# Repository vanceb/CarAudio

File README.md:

# CarAudio
Car Audio Using Raspberry Pi and a DAB Radio board

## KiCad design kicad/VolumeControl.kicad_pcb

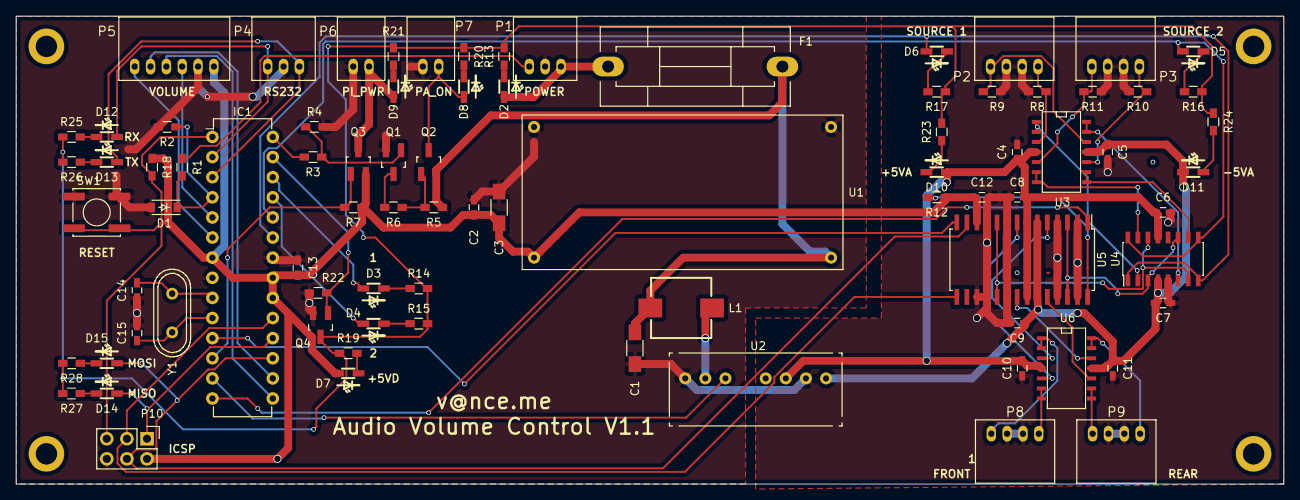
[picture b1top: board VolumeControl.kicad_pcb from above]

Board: 2 copper layers, 160.0 x 59.1 mm, 83 parts (0 on the bottom side), 70 nets.

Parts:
C1: 0.68u; C_1206_HandSoldering
C2, C4, C5, C6, C7, C8, C9, C10, C11, C12, C13: 0.1u; C_0603_HandSoldering
C3: 1u; C_1206_HandSoldering
C14, C15: 22p; C_0603_HandSoldering
D1: 5.1V; SOD-123
D2: +12V; LED_SMD_1.6x0.8mm
D3: 1; LED_SMD_1.6x0.8mm
D4: 2; LED_SMD_1.6x0.8mm
D5: S2; LED_SMD_1.6x0.8mm
D6: S1; LED_SMD_1.6x0.8mm
D7: +5VD; LED_SMD_1.6x0.8mm
D8: PA; LED_SMD_1.6x0.8mm
D9: PI; LED_SMD_1.6x0.8mm
D10: +5VA; LED_SMD_1.6x0.8mm
D11: -5VA; LED_SMD_1.6x0.8mm
D12: RX; LED_SMD_1.6x0.8mm
D13: TX; LED_SMD_1.6x0.8mm
D14: MISO; LED_SMD_1.6x0.8mm
D15: MOSI; LED_SMD_1.6x0.8mm
F1: 1A; Fuseholder5x20_horiz_SemiClosed_Casing10x25mm
IC1: ATMEGA328P-P; DIP-28_W7.62mm
L1: 10u; Inductor_SRR0735A
P1: PWR_IN; JST-3RA
P2: SOURCE_1; JST-4RA
P3: SOURCE_2; JST-4RA
P4: RS232; JST-3RA
P5: VOL_KNOB; JST-6RA
P6: PI_PWR; JST-2RA
P7: PA_EN; JST-2RA
P8: FRONT; JST-4RA
P9: REAR; JST-4RA
P10: ICSP; Pin_Header_Straight_2x03
Q1: BC848B; SOT-23_Handsoldering
Q2, Q3: NX2301P; SOT-23_Handsoldering
Q4: TSM2302CX; SOT-23_Handsoldering
R1, R3, R4, R5, R7, R18, R22: 10k; R_0603_HandSoldering
R2, R6: 22k; R_0603_HandSoldering
R8, R9, R10, R11, R12: 47k; R_0603_HandSoldering
R13, R20: 1k; R_0603_HandSoldering
R14, R15, R16, R17, R19, R21, R23, R24, R25, R26, R27, R28: 220; R_0603_HandSoldering
SW1: SW_PUSH; SW_SPST_EVPBF
U1: Buck_Converter
U2: TMR_3-1221; TMR_3
U3, U6: OPA1664; SOIC-14_N
U4: DG308; SOIC-16_3.9x9.9mm_Pitch1.27mm
U5: PGA4311; SOIC-28_7.5x17.9mm_Pitch1.27mm
Y1: 16MHz; Crystal_HC49-U_Vertical

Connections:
+5VA: C4.1, C6.1, C8.1, C10.1, D10.2, U2.6, U3.4, U4.13, U5.7, U5.22, U6.4
+5VD: C2.1, C3.1, C12.1, C13.1, D7.2, IC1.7, IC1.20, IC1.21, P5.1, P10.2, Q3.2, R7.2, R12.1, R18.1, U1.3, U5.12
-5VA: C5.2, C7.2, C9.2, C11.2, D11.1, U2.8, U3.11, U4.4, U5.6, U5.23, U6.11
/Audio Processing/CS: IC1.11, U5.14
/Audio Processing/LEFT_FRONT: P8.1, U6.1, U6.2
/Audio Processing/LEFT_REAR: P9.1, U6.8, U6.9
/Audio Processing/MUTE: IC1.14, U5.1
/Audio Processing/RIGHT_FRONT: P8.4, U6.6, U6.7
/Audio Processing/RIGHT_REAR: P9.4, U6.13, U6.14
/Audio Processing/SCLK: IC1.19, P10.3, U5.15
/Audio Processing/SDI: D15.2, IC1.17, P10.4, U5.13
/Audio Processing/SOURCE_1_ENABLE: D6.2, IC1.23, U4.1, U4.8
/Audio Processing/SOURCE_1_LEFT: P2.1, R8.1, U3.3
/Audio Processing/SOURCE_1_RIGHT: P2.4, R9.1, U3.12
/Audio Processing/SOURCE_2_ENABLE: D5.2, IC1.24, U4.9, U4.16
/Audio Processing/SOURCE_2_LEFT: P3.1, R10.1, U3.10
/Audio Processing/SOURCE_2_RIGHT: P3.4, R11.1, U3.5
/DIgital_Control/AUDIO_ENABLE: IC1.13, U2.3
/DIgital_Control/BTN: IC1.5, P5.3
/DIgital_Control/IGNITION: D1.1, IC1.4, R1.2, R2.1
/DIgital_Control/MISO: D14.2, IC1.18, P10.1
/DIgital_Control/NEO: IC1.6, P5.6
/DIgital_Control/PA_ENABLE: IC1.28, R3.2
/DIgital_Control/PI_ENABLE: IC1.12, Q3.1, R7.1
/DIgital_Control/RESET: IC1.1, P10.5, R18.2, SW1.2
/DIgital_Control/ROT_A: IC1.15, P5.4
/DIgital_Control/ROT_B: IC1.16, P5.5
/DIgital_Control/RX_IN: D12.2, IC1.2, P4.3
/DIgital_Control/TX_OUT: D13.2, IC1.3, P4.1
/Power/+5V_PI: D9.2, P6.1, Q3.3
/Power/+12V_IGNITION: P1.3, R1.1
/Power/+12V_PA_ENABLE: D8.2, P7.1, Q2.3
/Power/+12V_SUPPLY: D2.2, F1.1, P1.1
GND: C1.2, C2.2, C3.2, C4.2, C5.1, C6.2, C7.1, C8.2, C9.1, C10.2, C11.1, C12.2, C13.2, C14.1, C15.1, D1.2, IC1.8, IC1.22, P1.2, P2.2, P2.3, P3.2, P3.3, P4.2, P5.2, P6.2, P7.2, P8.2, P8.3, P9.2, P9.3, P10.6, Q1.2, Q4.2, R2.2, R4.2, R8.2, R9.2, R10.2, R11.2, R22.2, SW1.1, U1.2, U1.4, U2.1, U2.7, U4.5, U5.2, U5.4, U5.9, U5.11, U5.17, U5.18, U5.20, U5.25, U5.27
LED_GND: Q4.3, R13.2, R14.2, R15.2, R16.2, R17.2, R19.2, R20.1, R21.2, R23.2, R24.2, R25.2, R26.2, R27.2, R28.2
unnamed: C1.1, F1.2, L1.1, Q2.2, R5.1, U1.1
unnamed: C14.2, IC1.9, Y1.1
unnamed: C15.2, IC1.10, Y1.2
unnamed: D2.1, R13.1
unnamed: D3.1, R14.1
unnamed: D3.2, IC1.26
unnamed: D4.1, R15.1
unnamed: D4.2, IC1.25
unnamed: D5.1, R16.1
unnamed: D6.1, R17.1
unnamed: D7.1, R19.1
unnamed: D8.1, R20.2
unnamed: D9.1, R21.1
unnamed: D10.1, R23.1
unnamed: D11.2, R24.1
unnamed: D12.1, R25.1
unnamed: D13.1, R26.1
unnamed: D14.1, R27.1
unnamed: D15.1, R28.1
unnamed: IC1.27, Q4.1, R22.1
unnamed: L1.2, U2.2
unnamed: Q1.1, R3.1, R4.1
unnamed: Q1.3, R6.2
unnamed: Q2.1, R5.2, R6.1
unnamed: R12.2, U5.28
unnamed: U3.1, U3.2, U4.2
unnamed: U3.6, U3.7, U4.15
unnamed: U3.8, U3.9, U4.10
unnamed: U3.13, U3.14, U4.6
unnamed: U4.3, U4.11, U5.3, U5.26
unnamed: U4.7, U4.14, U5.10, U5.19
unnamed: U5.5, U6.3
unnamed: U5.8, U6.5
unnamed: U5.21, U6.12
unnamed: U5.24, U6.10

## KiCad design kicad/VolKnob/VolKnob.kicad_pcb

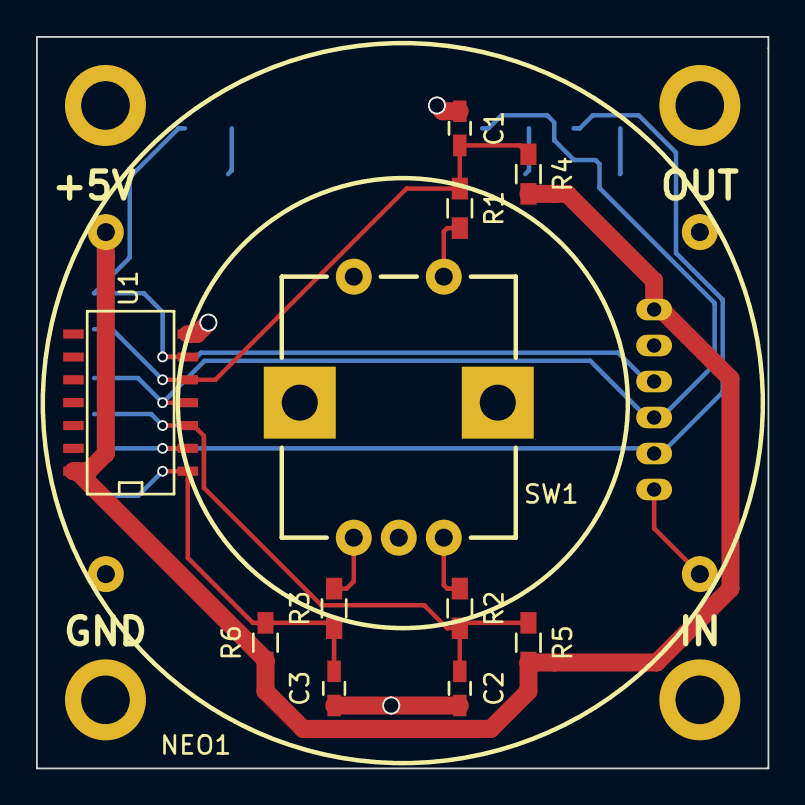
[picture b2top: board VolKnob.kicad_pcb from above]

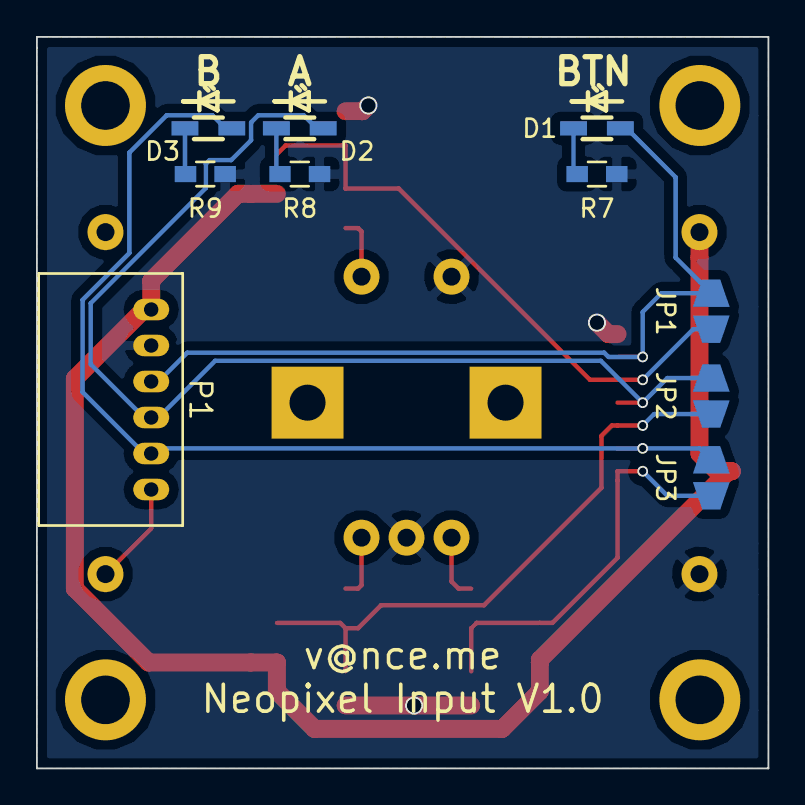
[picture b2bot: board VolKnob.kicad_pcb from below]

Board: 2 copper layers, 40.6 x 40.6 mm, 22 parts (10 on the bottom side), 15 nets.

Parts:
C1, C2, C3: 100n; C_0603_HandSoldering
D1, D2, D3: LED; LED_SMD_1.6x0.8mm
JP1, JP2, JP3: Jumper_NO_Small; Jumper_NO
NEO1: Neopixel; NeoPixel_Ring_12
P1: CONNECTOR; JST-6RA
R1, R2, R3: 2k2; R_0603_HandSoldering
R4, R5, R6: 10k; R_0603_HandSoldering
R7, R8, R9: 220; R_0603_HandSoldering
SW1: Rotary_Encoder
U1: 74HC14; SOIC-14_N

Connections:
+5V: NEO1.1, P1.1, R4.1, R5.1, R6.1, U1.14
/Btn: D1.2, JP1.2, P1.3, U1.6
/NEO: NEO1.3, P1.6
/ROT_A: D2.2, JP2.2, P1.4, U1.4
/ROT_B: D3.2, JP3.2, P1.5, U1.2
GND: C1.2, C2.2, C3.2, NEO1.2, P1.2, R7.1, R8.1, R9.1, SW1.2, SW1.4, U1.7
unnamed: C1.1, JP1.1, R1.1, R4.2, U1.5
unnamed: C2.1, JP2.1, R2.1, R5.2, U1.3
unnamed: C3.1, JP3.1, R3.1, R6.2, U1.1
unnamed: D1.1, R7.2
unnamed: D2.1, R8.2
unnamed: D3.1, R9.2
unnamed: R1.2, SW1.1
unnamed: R2.2, SW1.3
unnamed: R3.2, SW1.5

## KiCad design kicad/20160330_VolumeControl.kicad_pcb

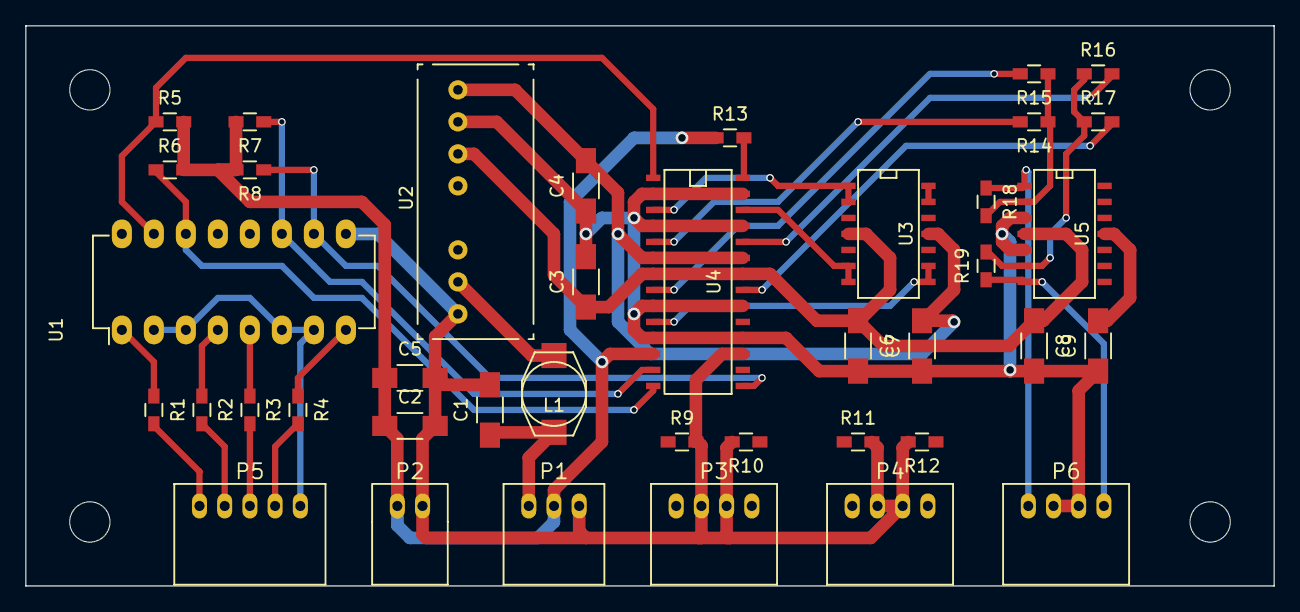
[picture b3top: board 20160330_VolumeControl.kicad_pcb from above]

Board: 2 copper layers, 99.1 x 44.5 mm, 40 parts (0 on the bottom side), 37 nets.

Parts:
C1: 0.68u; C_1206_HandSoldering
C2, C3, C4, C6, C7, C8, C9: 0.1u; C_1206_HandSoldering
C5: 1u; C_1206_HandSoldering
L1: 10u; SELF-WE-PD3S
P1: PWR_IN; JST-3RA
P2: PWR_OUT; JST-2RA
P3: SOURCE_1; JST-4RA
P4: SOURCE_2; JST-4RA
P5: CONTROL; JST-5RA
P6: AUDIO_OUT; JST-4RA
R1, R2, R3, R4: 200; R_0603_HandSoldering
R5, R6, R7, R8, R9, R10, R11, R12, R13, R14, R15, R16, R17, R18, R19: 47k; R_0603_HandSoldering
U1: ILQ74; DIP-16_W7.62mm_LongPads
U2: TMR_3-1221; TMR_3
U3, U5: OPA1664; SOIC-14_N
U4: PGA4311; SOIC-28

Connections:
+5VA: C3.1, C6.1, C8.1, U2.6, U3.4, U4.7, U4.22, U5.4
+5VD: C2.1, C5.1, P1.2, P2.1, R5.2, R6.2, R7.2, R8.2, R13.1, U4.12
+12V: C1.1, L1.1, P1.1
-5VA: C4.2, C7.2, C9.2, U2.8, U3.11, U4.6, U4.23, U5.11
/Audio Processing/CS_ISOLATED: R6.1, U1.14, U4.14
/Audio Processing/LEFT: P6.1, R18.1, U5.1
/Audio Processing/MUTE_ISOLATED: R5.1, U1.15, U4.1
/Audio Processing/RIGHT: P6.4, R19.1, U5.7
/Audio Processing/SCL_ISOLATED: R8.1, U1.10, U4.15
/Audio Processing/SDA_ISOLATED: R7.1, U1.11, U4.13
/Audio Processing/SOURCE_1_LEFT: P3.1, R9.1, U3.3
/Audio Processing/SOURCE_1_RIGHT: P3.4, R10.1, U3.5
/Audio Processing/SOURCE_2_LEFT: P4.1, R11.1, U3.10
/Audio Processing/SOURCE_2_RIGHT: P4.4, R12.1, U3.12
/Digital Control/CS: P5.2, R2.2
/Digital Control/CTRL_GND: P5.5, U1.2, U1.3, U1.6, U1.7
/Digital Control/MUTE: P5.1, R1.2
/Digital Control/SCL: P5.4, R4.2
/Digital Control/SDA: P5.3, R3.2
GNDA: C3.2, C4.1, C6.2, C7.1, C8.2, C9.1, P6.2, P6.3, U2.7, U4.2, U4.4, U4.9, U4.11, U4.18, U4.20, U4.25, U4.27, U5.3, U5.5
GNDD: C1.2, C2.2, C5.2, P1.3, P2.2, P3.2, P3.3, P4.2, P4.3, R9.2, R10.2, R11.2, R12.2, U1.9, U1.12, U1.13, U1.16, U2.1, U4.17
unnamed: L1.2, U2.2
unnamed: R1.1, U1.1
unnamed: R2.1, U1.4
unnamed: R3.1, U1.5
unnamed: R4.1, U1.8
unnamed: R13.2, U4.28
unnamed: R14.1, R15.1, R18.2, U5.2
unnamed: R14.2, U4.5
unnamed: R15.2, U4.8
unnamed: R16.1, R17.1, R19.2, U5.6
unnamed: R16.2, U4.24
unnamed: R17.2, U4.21
unnamed: U3.1, U3.2, U4.3
unnamed: U3.6, U3.7, U4.26
unnamed: U3.8, U3.9, U4.10
unnamed: U3.13, U3.14, U4.19

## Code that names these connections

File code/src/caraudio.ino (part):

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

// Neopixels
#define PIN_NEO 4
#define NUM_PIXELS 12 // Number of neopixels in the ring


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#define PI_DOWN_DELAY 60000 // 60 seconds

// Sensing
#define PIN_IGNITION 2
#define SHUTDOWN_DELAY 30000 // Decide to shutdown after ignition loss of 30 seconds
#define AUTO_SHUTDOWN_PERIOD 3600000 // 1 hour

// Notify
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#define ENDIAN MSBFIRST

// Hard Mute
#define PIN_MUTE 8

// Source selection
#define PIN_SOURCE_1 A0
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******************************************************************************/
enum machine_state {
    powering_up,        // Power just applied
    sleeping,           // Low power state for ignition off
    pi_up,              // Powering the Raspberry Pi up
    pi_down,            // Powering the Raspberry Pi down
    standby,            // State for ignition on
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char buffRx[256];

// Define the Neopixels
Adafruit_NeoPixel ring = Adafruit_NeoPixel(NUM_PIXELS, PIN_NEO, NEO_GRB + NEO_KHZ800);
uint32_t colour;
uint32_t walk_colour;
uint8_t brightness;
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    pinMode(PIN_PI_PWR, OUTPUT);
    pinMode(PIN_SOURCE_1, OUTPUT);
    pinMode(PIN_SOURCE_2, OUTPUT);
    pinMode(PIN_MUTE, OUTPUT);
    audio_off();
    pi_off();

    // Setup the input Sensing
    pinMode(PIN_IGNITION, INPUT);

    // Setup volume control knob pins
    pinMode(PIN_PUSH, INPUT);
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    sleep_enable();

    // Attach external interrupts that will wake us
    attachInterrupt(digitalPinToInterrupt(PIN_IGNITION), wake_up, RISING);
    attachInterrupt(digitalPinToInterrupt(PIN_PUSH), wake_up, FALLING);
    // Clear any queued interrupts that would wake us immediately
    EIFR = bit (INTF0);  // clear flag for interrupt 0
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// Wake form sleep
void wake_up() {
    noInterrupts();
    detachInterrupt(digitalPinToInterrupt(PIN_IGNITION));
    detachInterrupt(digitalPinToInterrupt(PIN_PUSH));

    // Check how we were woken
    if (digitalRead(PIN_IGNITION) == false) {
        // Assume we were woken by the PUSH_BUTTON
        // So allow us to be on without the ignition
        // For a set timeperiod at least
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    // Setup
    uint8_t a = digitalRead(PIN_ROTARY_A);
    uint8_t b = digitalRead(PIN_ROTARY_B);
    uint8_t btn = digitalRead(PIN_PUSH);

    uint8_t position = state(a,b);

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}

bool should_shutdown() {
    if (digitalRead(PIN_IGNITION) == 1) {
        // Ignition is on so give ourselves a grace time
        // in case Ignition is turned off briefly
        auto_shutdown_millis = millis() + SHUTDOWN_DELAY;
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    hard_muted = true;
    // Flag if muted
    digitalWrite(PIN_LED_2, soft_muted | hard_muted);
    pinMode(PIN_MUTE, OUTPUT);
    digitalWrite(PIN_MUTE, LOW);
}

void hard_unmute() {
    hard_muted = false;
    // Flag if muted
    digitalWrite(PIN_LED_2, soft_muted | hard_muted);
    pinMode(PIN_MUTE, OUTPUT);
    digitalWrite(PIN_MUTE, HIGH);
}

/**************************************************************************
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
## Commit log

2016-02-23 Initial Audio Board Design in Kicad, still WIP
2016-05-11 Adding untracked files
2016-05-11 Removed extra directory needed for Arduino IDE to revert to Platformio project
2016-06-12 First working version of using a timer to debounce the rotary encoder
2016-06-12 Created Rotary Encoder with Neopixel ring PCB for Volume control
2016-06-13 Modified circuit to allow for hardware debounce
2016-06-14 Reworked schematics to allow control of the power and introduction of ATMega328P for control
2016-06-15 Produced Volume knob including Gerbers, and updated main board to remove ERC errors. Just about to start board layout
2016-06-15 Routed the board. Passes ERC check
2016-06-15 Minor change
2016-06-15 Gerber files created
2016-06-15 Slightly tweaked silkscreen and regenerated gerbers
2016-06-16 Updated to include extra indicator LEDs controlled by the ATMega. PCB reworked
2016-06-23 Minor updates and board submitted for fabrication
2016-06-23 basic board tests
2016-07-01 Updated board design with some footprint changes and improved audio layout
2016-07-08 Removed .DS_Store
2016-07-13 Slightly modified to include powering on and off the audio power
2016-08-18 Initial working state machine for powering on and off the device and internal compoents
2016-08-18 Changed to bitbanging SPI as I have pin conflicts on the board
2016-08-19 Updated to allow changing sources and muting via the control knob. Also introduced ability to start without ignition being on. System will come up for an hour before shutting down again, unless ignit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
